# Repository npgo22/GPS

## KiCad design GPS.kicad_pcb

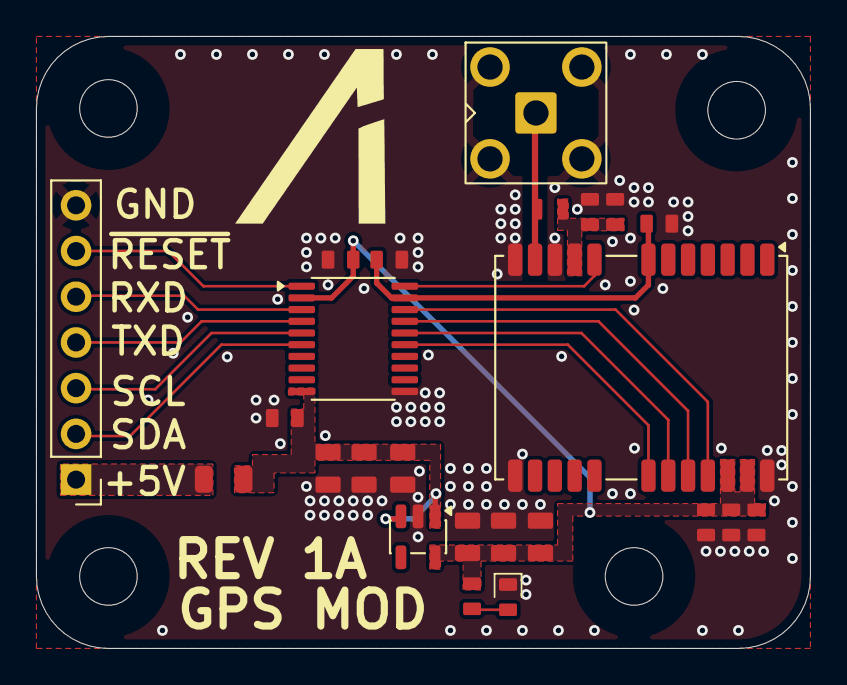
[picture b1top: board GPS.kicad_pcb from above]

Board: 4 copper layers, 43.0 x 34.0 mm, 28 parts (0 on the bottom side), 18 nets.

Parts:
C1, C2, C3, C5, C7, C9: 22uF; C_0805
C4, C6, C8, C12, C14: 100nF; C_0603
C10, C11: 33pF; C_0603
C13: 100pF; C_0603
D1: LED_Small; LED_0603
F1: 100mA hold; Fuse_0805_2012Metric
H1, H2, H3, H4: MountingHole; MountingHole_3.2mm_M3
J1: Conn_01x07; PinHeader_1x07_P2.54mm_Vertical
J2: SMA; SMA_BAT_Wireless_BWSMA-KWE-Z001
L1: 68 nH; LQW18AN68NG8Z
R1, R2: 10k; R_0603
U1: AP2112K-3.3; SOT-23-5
U2: TXS0108EPW; TSSOP-20_4.4x6.5mm_P0.65mm
U3: LC29H; ublox_NEO

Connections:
+2.8V: C6.1, C12.1, U2.19 (VCCB), U3.7 (VDD_EXT)
+3.3V: C4.1, C5.1, C7.1, C8.1, C9.1, C10.1, C11.1, R2.1, U1.5 (VOUT), U2.2 (VCCA), U3.22 (V_BCKP), U3.23 (VCC)
+5V: C1.1, C2.1, C3.1, F1.1, R1.1, U1.1 (VIN), U1.3 (EN), U2.10 (OE)
/I2C_SCL: U2.16 (B4), U3.19 (I2C_SCL)
/I2C_SDA: U2.15 (B5), U3.18 (I2C_SDA)
/RXD: U2.18 (B2), U3.21 (RXD)
/TXD: U2.17 (B3), U3.20 (TXD)
/~RESET: U2.20 (B1), U3.8 (~RESET)
GND: C1.2, C2.2, C3.2, C4.2, C5.2, C6.2, C7.2, C8.2, C9.2, C10.2, C11.2, C12.2, C13.2, C14.2, D1.1 (K), J1.7, J2.2 (Ext), R1.2, U1.2 (GND), U2.11 (GND), U3.10 (GND), U3.12 (GND), U3.13 (GND), U3.24 (GND)
unnamed: D1.2 (A), R2.2
unnamed: F1.2, J1.1
unnamed: J1.2, U2.6 (A5)
unnamed: J1.3, U2.5 (A4)
unnamed: J1.4, U2.4 (A3)
unnamed: J1.5, U2.3 (A2)
unnamed: J1.6, U2.1 (A1)
unnamed: J2.1 (In), L1.2, U3.11 (RF_IN)
unnamed: C13.1, C14.1, L1.1, U3.9 (VDD_RF)

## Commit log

2026-01-18 Re-annotate board
2026-01-19 Clean up area underneath antenna
2026-01-19 Make the antenna area symmetrical
